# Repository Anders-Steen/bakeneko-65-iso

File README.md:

## ⚠️ Warning not finished ⚠️
I want to make my own ISO version of the Bakenko 65%.
Make it wireless.
[X] Decide on a ISO layout
[] ~ Replace daughterboard with mcu+interface ~
[X] Update PCB
[] ~ Update case ~ 

# Bakeneko 65 V4 - ISO

A simple 65% keyboard for DIYers. This project is a special homage to TGR x Singa UNIKORN 60 and OTD 356 Mini. See also the [introduction video](https://youtu.be/o677NcIUri4).

## Features

- Single piece tray case
- O-ring gasket mount (Friction fit)
- [Unified Daughterboard](https://github.com/ai03-2725/Unified-Daughterboard)
- ~QMK firmware and VIA~ ZMK
- PCB designed with KiCAD ~5.1.4~ 10.0

## Layout

## Specs

- Dimensions: 315 x 110 x 30mm
- Front height: 18.5mm
- Home row height: 31mm(with GMK keycaps and bumpons)
- Typing angle: 6 degree
- Weight:
  - PLA Case: 390g
  - Aluminum Case: 760g
- O-ring gasket: VMQ-50(Silicone 50 duro) AS568-264
- MCU: NRF52840

## Notes
- Old files (v1) are no longer available. See [geekhack post](https://geekhack.org/index.php?topic=107316.msg2974824#msg2974824) for the context
- The use of old (v1) mounting posts is prohibited
- All files are to be used at your own risk
- As for stabilizers, only PCB snap ins are supported

## Resources

- Documents: https://drive.google.com/drive/folders/1tddSihOS8Pgf1lTQOjHohYCl8efxXIeH
  - Parts guide and other useful information
  - Will be added and updated as needed
- Discord: https://discord.gg/fMY96TeEwV
  - Have fun with community members
  - Talk about Bakeneko builds and mods, and share your works
  - You can also contact me from there

## Special thanks to

- **Elaine** for [Unikorn](https://geekhack.org/index.php?topic=98587.50). Allowed me to publish the Unikorn-inspired case as open source and encouraged me
- Of course, I also show my respect and gratitude to **yuktsi**
- **coarse** for PCB review and kind support. His great work has refined the PCB well

## Also I should mention

- **OTD** for 356 Mini. Origin of O-ring gasket mount style
- **Evy** for [Plain60 series](https://github.com/evyd13/plain60-c). I used it as a reference for my PCB design. They also answered my miscellaneous questions
- **ai03** for [MX_Alps_Hybrid](https://github.com/ai03-2725/MX_Alps_Hybrid). Also got a lot of help from his discord server
- **overset** for [JP01](https://github.com/overset/JP01). The idea of publishing the case design on Onshape. After seeing their great work I switched from fusion360 to Onshape
- **Rhuk** gave me a lot of advice on keyboard design and manufacturing
- **Maker Keyboards** suggested adding a plate cutout to remove the PCB using a keycap puller
- And many community members for giving me advice and feedback, thanks!

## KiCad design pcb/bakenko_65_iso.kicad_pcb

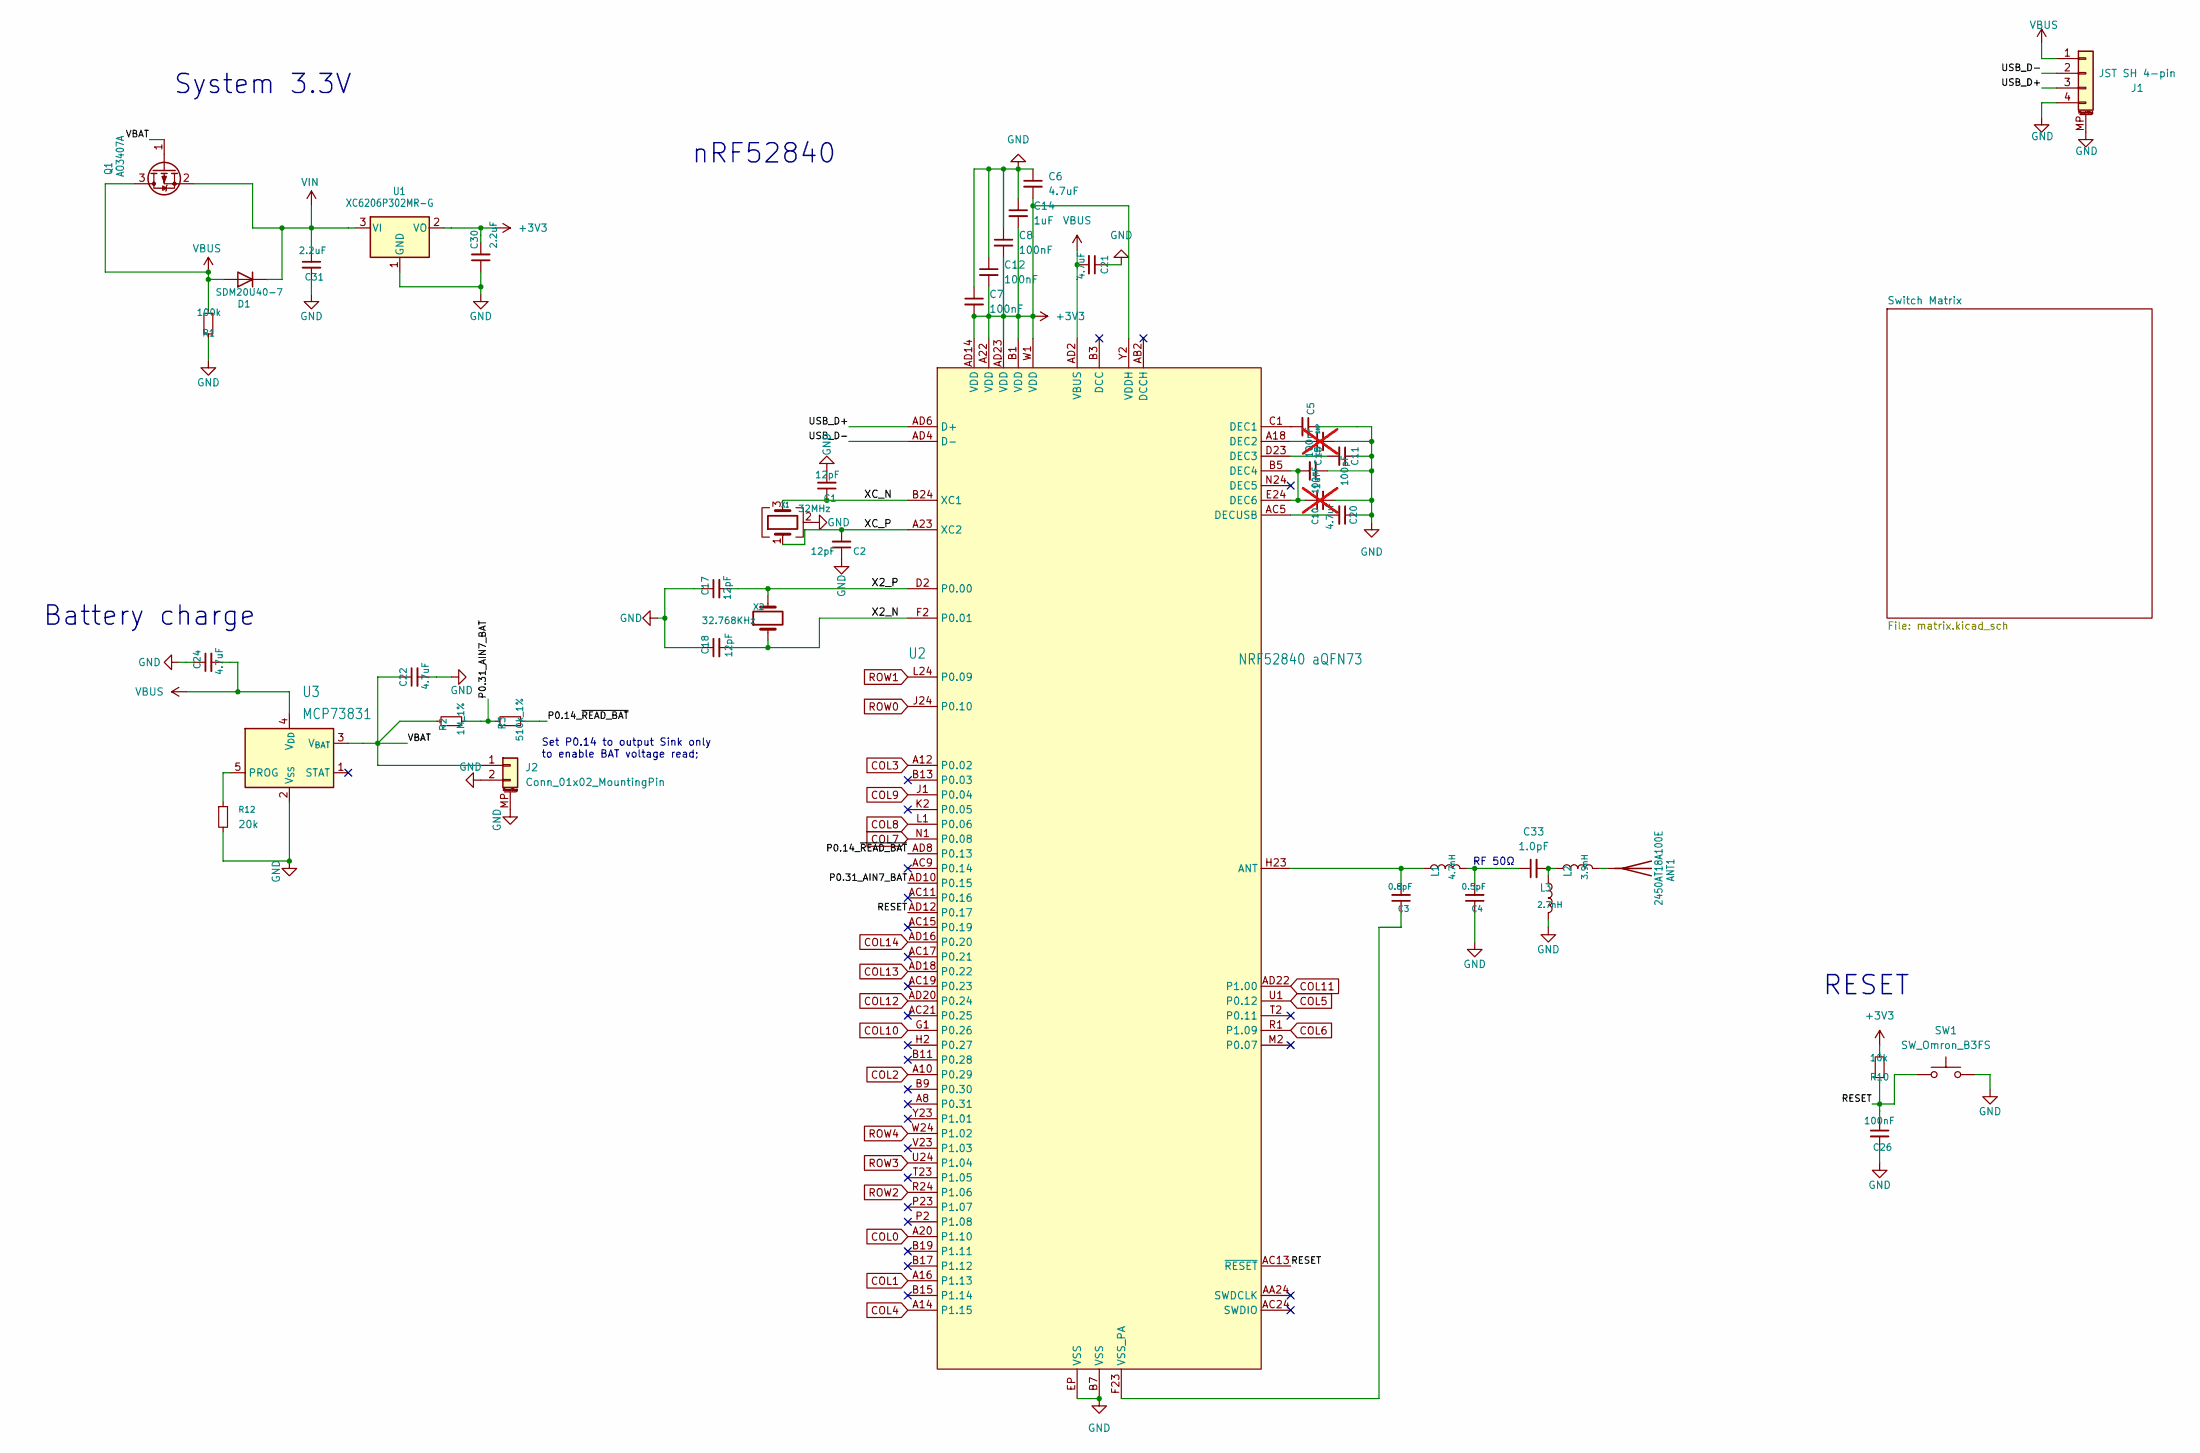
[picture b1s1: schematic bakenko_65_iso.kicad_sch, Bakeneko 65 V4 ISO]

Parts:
ANT1: 2450AT18A100E; Johanson_2450AT18x100_2400-2500Mhz
C1, C2, C17, C18: 12pF; C_0402_1005Metric
C3: 0.8pF; C_0402_1005Metric
C4: 0.5pF; C_0402_1005Metric
C5, C7, C8, C12, C26: 100nF; C_0402_1005Metric
C6, C20, C21: 4.7uF; C_0603_1608Metric
C10: 100nF; C_0402_1005Metric; not fitted
C11: 100pF; C_0402_1005Metric
C13: DNP; C_0402_1005Metric; not fitted
C14, C15: 1uF; C_0603_1608Metric
C22, C24: 4.7uF; C_0402_1005Metric
C30, C31: 2.2uF; C_0402_1005Metric
C33: 1.0pF; C_0402_1005Metric
D1: SDM20U40-7; D_SOD-523
J1: JST SH 4-pin; Molex_Pico-EZmate_78171-0004_1x04-1MP_P1.20mm_Vertical; LCSC Part # C160404
J2: Conn_01x02_MountingPin; Molex_Pico-EZmate_78171-0002_1x02-1MP_P1.20mm_Vertical
L1: 4.7nH; L_0402_1005Metric
L2: 3.9nH; L_0402_1005Metric
L3: 2.7nH; L_0402_1005Metric
Q1: AO3407A; SOT-23
R1: 100k; R_0402_1005Metric
R2: 1M_1%; R_0402_1005Metric
R3: 510k_1%; R_0402_1005Metric
R10: 10k; R_0402_1005Metric
R12: 20k; R_0402_1005Metric
SW1: SW_Omron_B3FS; SW_SPST_TS-1088-xR020
U1: XC6206P302MR-G; SOT-23
U2: NRF52840 aQFN73; Nordic_AQFN-73-1EP_7x7mm_P0.5mm
U3: MCP73831; SOT-23-5; MPN BQ25101YFPT
X1: 32MHz; Crystal_SMD_2016-4Pin_2.0x1.6mm
X2: 32.768KHz; Crystal_SMD_3215-2Pin_3.2x1.5mm

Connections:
+3V3: C6.2, C7.2, C8.2, C12.2, C14.2, C30.2, R10.2, U1.2 (VO), U2.A22 (VDD), U2.AD14 (VDD), U2.AD23 (VDD), U2.B1 (VDD), U2.W1 (VDD), U2.Y2 (VDDH)
/P0.14_~READ_BAT: R3.2, U2.AD8 (P0.13)
/P0.31_AIN7_BAT: R2.2, R3.1, U2.AD10 (P0.15)
/RESET: C26.1, R10.1, SW1.1, U2.AC13 (~RESET), U2.AD12 (P0.17)
/USB_D+: J1.3, U2.AD6 (D+)
/USB_D-: J1.2, U2.AD4 (D-)
/VBAT: C22.1, J2.1, Q1.1 (G), R2.1, U3.3 (V_{BAT})
/X2_N: C18.2, U2.F2 (P0.01), X2.1
/X2_P: C17.2, U2.D2 (P0.00), X2.2
/XC_N: C1.1, U2.B24 (XC1), X1.3
/XC_P: C2.2, U2.A23 (XC2), X1.1
COL0: U2.A20 (P1.10); also elsewhere on the board
COL1: U2.A16 (P1.13); also elsewhere on the board
COL2: U2.A10 (P0.29); also elsewhere on the board
COL3: U2.A12 (P0.02); also elsewhere on the board
COL4: U2.A14 (P1.15); also elsewhere on the board
COL5: U2.U1 (P0.12); also elsewhere on the board
COL6: U2.R1 (P1.09); also elsewhere on the board
COL7: U2.N1 (P0.08); also elsewhere on the board
COL8: U2.L1 (P0.06); also elsewhere on the board
COL9: U2.J1 (P0.04); also elsewhere on the board
COL10: U2.G1 (P0.26); also elsewhere on the board
COL11: U2.AD22 (P1.00); also elsewhere on the board
COL12: U2.AD20 (P0.24); also elsewhere on the board
COL13: U2.AD18 (P0.22); also elsewhere on the board
COL14: U2.AD16 (P0.20); also elsewhere on the board
GND: C1.2, C2.1, C4.1, C5.1, C6.1, C7.1, C8.1, C10.2, C11.1, C12.1, C13.2, C14.1, C15.1, C17.1, C18.1, C20.1, C21.1, C22.2, C24.1, C26.2, C30.1, C31.2, J1.4, J1.MP (MountPin), J2.2, J2.MP (MountPin), L3.2, R1.2, R12.2, SW1.2, U1.1 (GND), U2.B7 (VSS), U2.EP (VSS), U3.2 (V_{SS}), X1.2 (G), X1.4 (G)
unnamed: ANT1.1 (A_1), L2.2
unnamed: C4.2, C33.1, L1.2
unnamed: C33.2, L2.1, L3.1
unnamed: C3.2, L1.1, U2.H23 (ANT)
unnamed: C5.2, U2.C1 (DEC1)
unnamed: C13.1, U2.A18 (DEC2)
unnamed: C11.2, U2.D23 (DEC3)
unnamed: C10.1, C15.2, U2.B5 (DEC4), U2.E24 (DEC6)
unnamed: C20.2, U2.AC5 (DECUSB)
unnamed: C3.1, U2.F23 (VSS_PA)
unnamed: R12.1, U3.5 (PROG)
ROW0: U2.J24 (P0.10); also elsewhere on the board
ROW1: U2.L24 (P0.09); also elsewhere on the board
ROW2: U2.R24 (P1.06); also elsewhere on the board
ROW3: U2.U24 (P1.04); also elsewhere on the board
ROW4: U2.W24 (P1.02); also elsewhere on the board
VBUS: C21.2, C24.2, D1.2 (A), J1.1, Q1.3 (D), R1.1, U2.AD2 (VBUS), U3.4 (V_{DD})
VIN: C31.1, D1.1 (K), Q1.2 (S), U1.3 (VI)

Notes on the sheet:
nRF52840
Battery charge
System 3.3V
RESET
RF 50Ω
Set P0.14 to output Sink only to enable BAT voltage read;

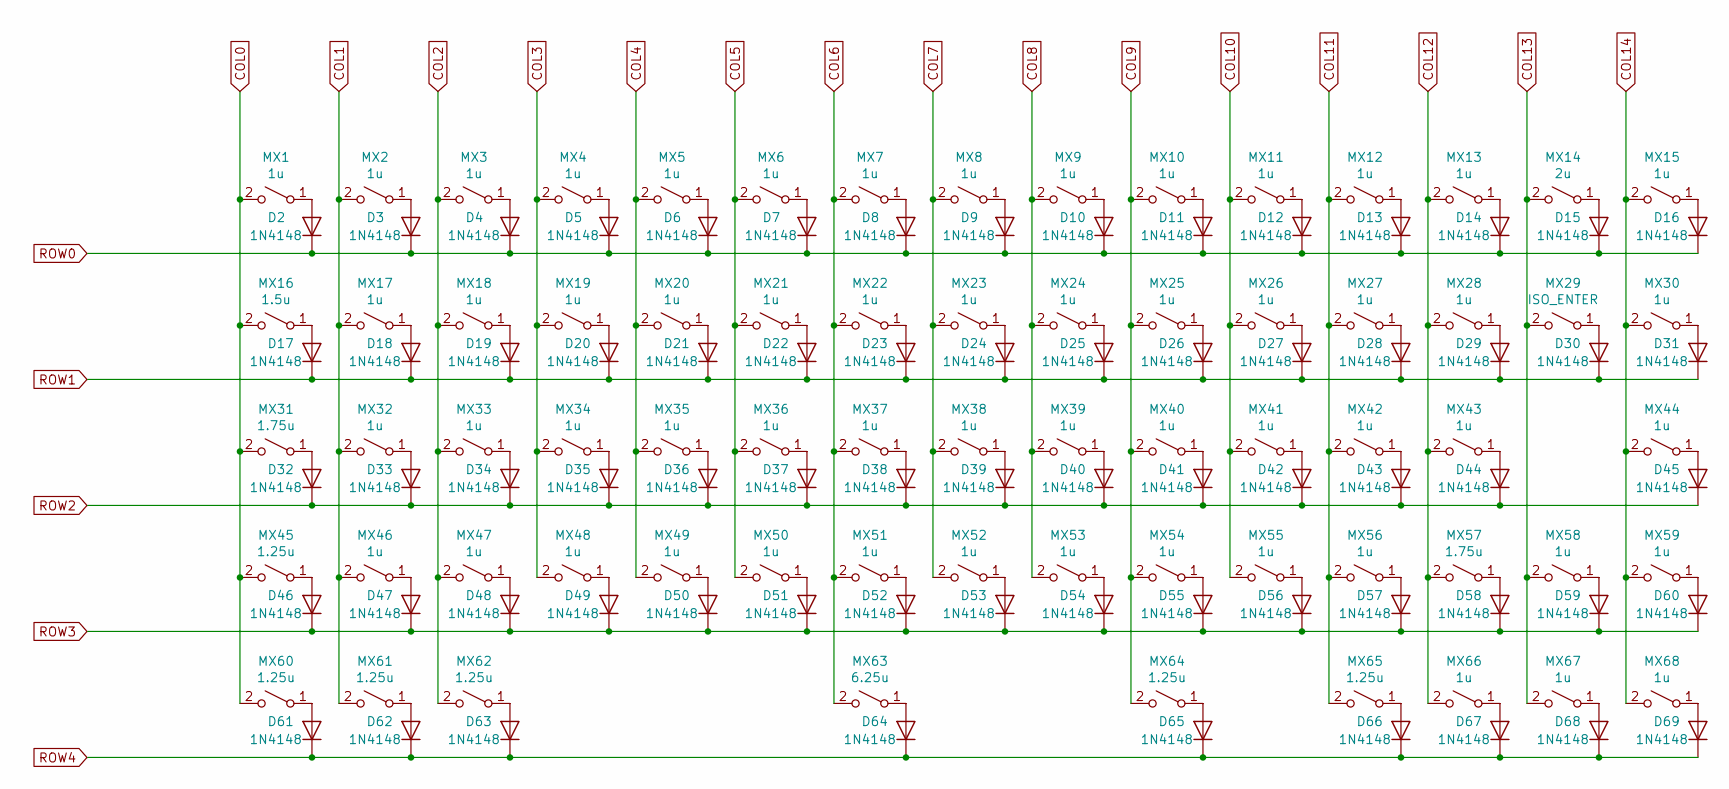
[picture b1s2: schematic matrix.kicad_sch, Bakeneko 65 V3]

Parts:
D2, D3, D4, D5, D6, D7, D8, D9, D10, D11, D12, D13, D14, D15, D16, D17, D18, D19, D20, D21, D22, D23, D24, D25, D26, D27, D28, D29, D30, D31, D32, D33, D34, D35, D36, D37, D38, D39, D40, D41, D42, D43, D44, D45, D46, D47, D48, D49, D50, D51, D52, D53, D54, D55, D56, D57, D58, D59, D60, D61, D62, D63, D64, D65, D66, D67, D68, D69: 1N4148; D_SOD-123; LCSC Part # C81598
MX1, MX2, MX3, MX4, MX5, MX6, MX7, MX8, MX9, MX10, MX11, MX12, MX13, MX15, MX17, MX18, MX19, MX20, MX21, MX22, MX23, MX24, MX25, MX26, MX27, MX28, MX30, MX32, MX33, MX34, MX35, MX36, MX37, MX38, MX39, MX40, MX41, MX42, MX43, MX44, MX46, MX47, MX48, MX49, MX50, MX51, MX52, MX53, MX54, MX55, MX56, MX58, MX59, MX66, MX67, MX68: 1u; SW_MX_1u
MX14: 2u; SW_MX_1u
MX16: 1.5u; SW_MX_1.5u
MX29: ISO_ENTER; SW_MX_1u
MX31, MX57: 1.75u; SW_MX_1.75u
MX45, MX60, MX61, MX62, MX64, MX65: 1.25u; SW_MX_1.25u
MX63: 6.25u; SW_MX_1u

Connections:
COL0: MX1.2 (B), MX16.2 (B), MX31.2 (B), MX45.2 (B), MX60.2 (B); also elsewhere on the board
COL1: MX2.2 (B), MX17.2 (B), MX32.2 (B), MX46.2 (B), MX61.2 (B); also elsewhere on the board
COL2: MX3.2 (B), MX18.2 (B), MX33.2 (B), MX47.2 (B), MX62.2 (B); also elsewhere on the board
COL3: MX4.2 (B), MX19.2 (B), MX34.2 (B), MX48.2 (B); also elsewhere on the board
COL4: MX5.2 (B), MX20.2 (B), MX35.2 (B), MX49.2 (B); also elsewhere on the board
COL5: MX6.2 (B), MX21.2 (B), MX36.2 (B), MX50.2 (B); also elsewhere on the board
COL6: MX7.2 (B), MX22.2 (B), MX37.2 (B), MX51.2 (B), MX63.2 (B); also elsewhere on the board
COL7: MX8.2 (B), MX23.2 (B), MX38.2 (B), MX52.2 (B); also elsewhere on the board
COL8: MX9.2 (B), MX24.2 (B), MX39.2 (B), MX53.2 (B); also elsewhere on the board
COL9: MX10.2 (B), MX25.2 (B), MX40.2 (B), MX54.2 (B), MX64.2 (B); also elsewhere on the board
COL10: MX11.2 (B), MX26.2 (B), MX41.2 (B), MX55.2 (B); also elsewhere on the board
COL11: MX12.2 (B), MX27.2 (B), MX42.2 (B), MX56.2 (B), MX65.2 (B); also elsewhere on the board
COL12: MX13.2 (B), MX28.2 (B), MX43.2 (B), MX57.2 (B), MX66.2 (B); also elsewhere on the board
COL13: MX14.2 (B), MX29.2 (B), MX58.2 (B), MX67.2 (B); also elsewhere on the board
COL14: MX15.2 (B), MX30.2 (B), MX44.2 (B), MX59.2 (B), MX68.2 (B); also elsewhere on the board
unnamed: D2.2 (A), MX1.1 (A)
unnamed: D3.2 (A), MX2.1 (A)
unnamed: D4.2 (A), MX3.1 (A)
unnamed: D5.2 (A), MX4.1 (A)
unnamed: D6.2 (A), MX5.1 (A)
unnamed: D7.2 (A), MX6.1 (A)
unnamed: D8.2 (A), MX7.1 (A)
unnamed: D9.2 (A), MX8.1 (A)
unnamed: D10.2 (A), MX9.1 (A)
unnamed: D11.2 (A), MX10.1 (A)
unnamed: D12.2 (A), MX11.1 (A)
unnamed: D13.2 (A), MX12.1 (A)
unnamed: D14.2 (A), MX13.1 (A)
unnamed: D15.2 (A), MX14.1 (A)
unnamed: D16.2 (A), MX15.1 (A)
unnamed: D17.2 (A), MX16.1 (A)
unnamed: D18.2 (A), MX17.1 (A)
unnamed: D19.2 (A), MX18.1 (A)
unnamed: D20.2 (A), MX19.1 (A)
unnamed: D21.2 (A), MX20.1 (A)
unnamed: D22.2 (A), MX21.1 (A)
unnamed: D23.2 (A), MX22.1 (A)
unnamed: D24.2 (A), MX23.1 (A)
unnamed: D25.2 (A), MX24.1 (A)
unnamed: D26.2 (A), MX25.1 (A)
unnamed: D27.2 (A), MX26.1 (A)
unnamed: D28.2 (A), MX27.1 (A)
unnamed: D29.2 (A), MX28.1 (A)
unnamed: D30.2 (A), MX29.1 (A)
unnamed: D31.2 (A), MX30.1 (A)
unnamed: D32.2 (A), MX31.1 (A)
unnamed: D33.2 (A), MX32.1 (A)
unnamed: D34.2 (A), MX33.1 (A)
unnamed: D35.2 (A), MX34.1 (A)
unnamed: D36.2 (A), MX35.1 (A)
unnamed: D37.2 (A), MX36.1 (A)
unnamed: D38.2 (A), MX37.1 (A)
unnamed: D39.2 (A), MX38.1 (A)
unnamed: D40.2 (A), MX39.1 (A)
unnamed: D41.2 (A), MX40.1 (A)
unnamed: D42.2 (A), MX41.1 (A)
unnamed: D43.2 (A), MX42.1 (A)
unnamed: D44.2 (A), MX43.1 (A)
unnamed: D45.2 (A), MX44.1 (A)
unnamed: D46.2 (A), MX45.1 (A)
unnamed: D47.2 (A), MX46.1 (A)
unnamed: D48.2 (A), MX47.1 (A)
unnamed: D49.2 (A), MX48.1 (A)
unnamed: D50.2 (A), MX49.1 (A)
unnamed: D51.2 (A), MX50.1 (A)
unnamed: D52.2 (A), MX51.1 (A)
unnamed: D53.2 (A), MX52.1 (A)
unnamed: D54.2 (A), MX53.1 (A)
unnamed: D55.2 (A), MX54.1 (A)
unnamed: D56.2 (A), MX55.1 (A)
unnamed: D57.2 (A), MX56.1 (A)
unnamed: D58.2 (A), MX57.1 (A)
unnamed: D59.2 (A), MX58.1 (A)
unnamed: D60.2 (A), MX59.1 (A)
unnamed: D61.2 (A), MX60.1 (A)
unnamed: D62.2 (A), MX61.1 (A)
unnamed: D63.2 (A), MX62.1 (A)
unnamed: D64.2 (A), MX63.1 (A)
unnamed: D65.2 (A), MX64.1 (A)
unnamed: D66.2 (A), MX65.1 (A)
unnamed: D67.2 (A), MX66.1 (A)
unnamed: D68.2 (A), MX67.1 (A)
unnamed: D69.2 (A), MX68.1 (A)
ROW0: D2.1 (K), D3.1 (K), D4.1 (K), D5.1 (K), D6.1 (K), D7.1 (K), D8.1 (K), D9.1 (K), D10.1 (K), D11.1 (K), D12.1 (K), D13.1 (K), D14.1 (K), D15.1 (K), D16.1 (K); also elsewhere on the board
ROW1: D17.1 (K), D18.1 (K), D19.1 (K), D20.1 (K), D21.1 (K), D22.1 (K), D23.1 (K), D24.1 (K), D25.1 (K), D26.1 (K), D27.1 (K), D28.1 (K), D29.1 (K), D30.1 (K), D31.1 (K); also elsewhere on the board
ROW2: D32.1 (K), D33.1 (K), D34.1 (K), D35.1 (K), D36.1 (K), D37.1 (K), D38.1 (K), D39.1 (K), D40.1 (K), D41.1 (K), D42.1 (K), D43.1 (K), D44.1 (K), D45.1 (K); also elsewhere on the board
ROW3: D46.1 (K), D47.1 (K), D48.1 (K), D49.1 (K), D50.1 (K), D51.1 (K), D52.1 (K), D53.1 (K), D54.1 (K), D55.1 (K), D56.1 (K), D57.1 (K), D58.1 (K), D59.1 (K), D60.1 (K); also elsewhere on the board
ROW4: D61.1 (K), D62.1 (K), D63.1 (K), D64.1 (K), D65.1 (K), D66.1 (K), D67.1 (K), D68.1 (K), D69.1 (K); also elsewhere on the board

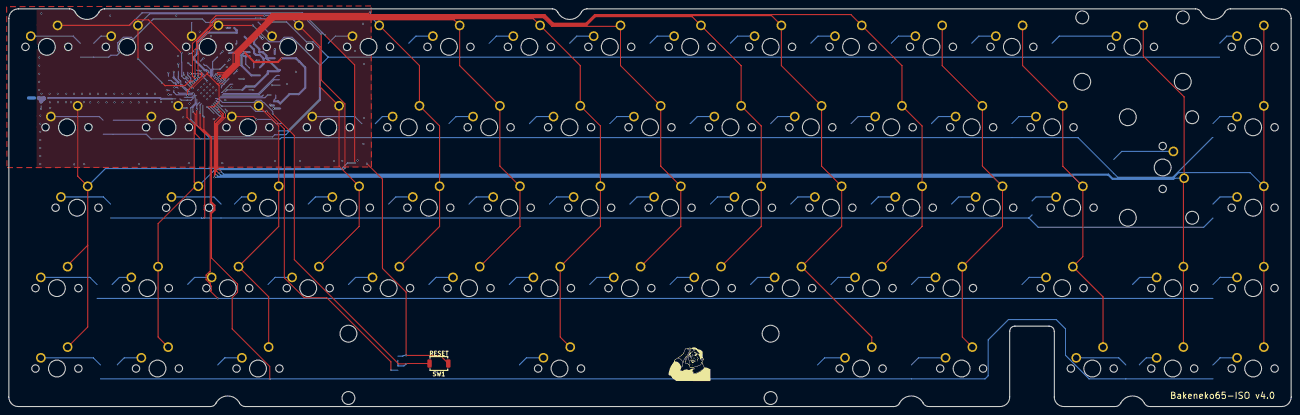
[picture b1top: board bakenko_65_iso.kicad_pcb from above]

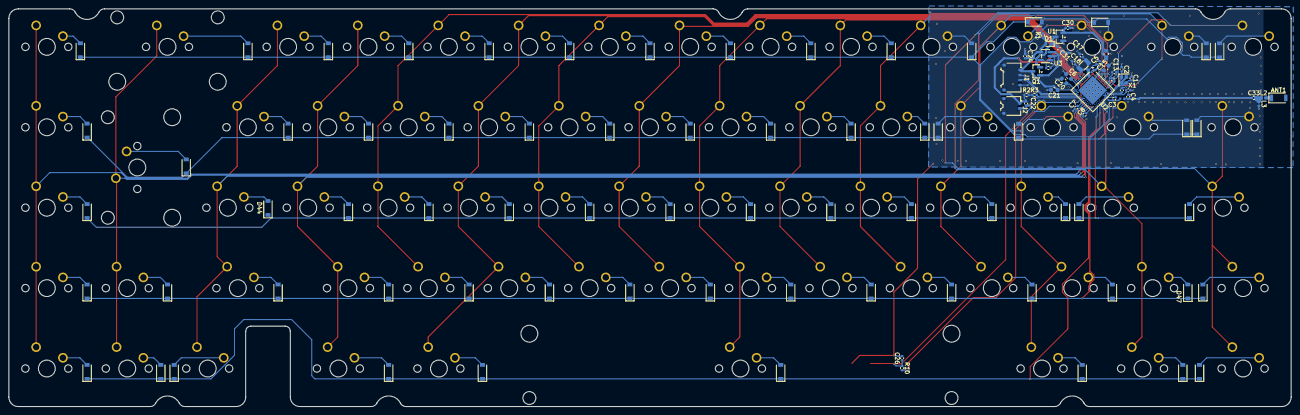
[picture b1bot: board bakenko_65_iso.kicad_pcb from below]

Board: 2 copper layers, 303.8 x 94.2 mm, 179 parts (110 on the bottom side), 113 nets.

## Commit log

2026-02-19 Removed ANSI production files
2026-04-06 WIP + Cleaned repository
2026-04-07 🧹Cleaned more up and updated the readme
2026-04-08 Cleaning zones and moving antenna
2026-04-09 Connecting reset and reducing errors and warnings
2026-04-13 Adding changes thanks to comment from devzone nordic
2026-04-13 Removed .history
2026-04-13 Adding iso layout
2026-05-12 Final changes before pcb-assebly

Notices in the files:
bakenko_65_iso/bakenko_65_iso.kicad_sch:
Copyright © 2020 kkatano
MIT License
